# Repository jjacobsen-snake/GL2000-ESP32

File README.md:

# GL2000-ESP32
GL2000 ESP32 WiFi Module

Schematic and PCB designed by me, surrounding [netmindz project](https://github.com/netmindz/balboa_GL_ML_spa_control)

## Pin configuration:
* GPIO 0 - BOOT Button
* GPIO 1 - TxD / USB via FT230XQ
* GPIO 2 - Status LED
* GPIO 3 - RxD / USB via FT230XQ
* GPIO 4 - RD / MAX485E RD
* GPIO 13 - (Pin 4 - Digital pin) Via level shifter
* GPIO 14 - (Pin 5 - Main panel port selector) Via level shifter
* GPIO 16 - RxD2 / MAX485E Tx
* GPIO 17 - TxD2 / MAX485E Rx
* GPIO 21 - SDA / I2C used for BME280, BME680 or SHT45
* GPIO 22 - SCL / I2C used for BME280, BME680 or SHT45

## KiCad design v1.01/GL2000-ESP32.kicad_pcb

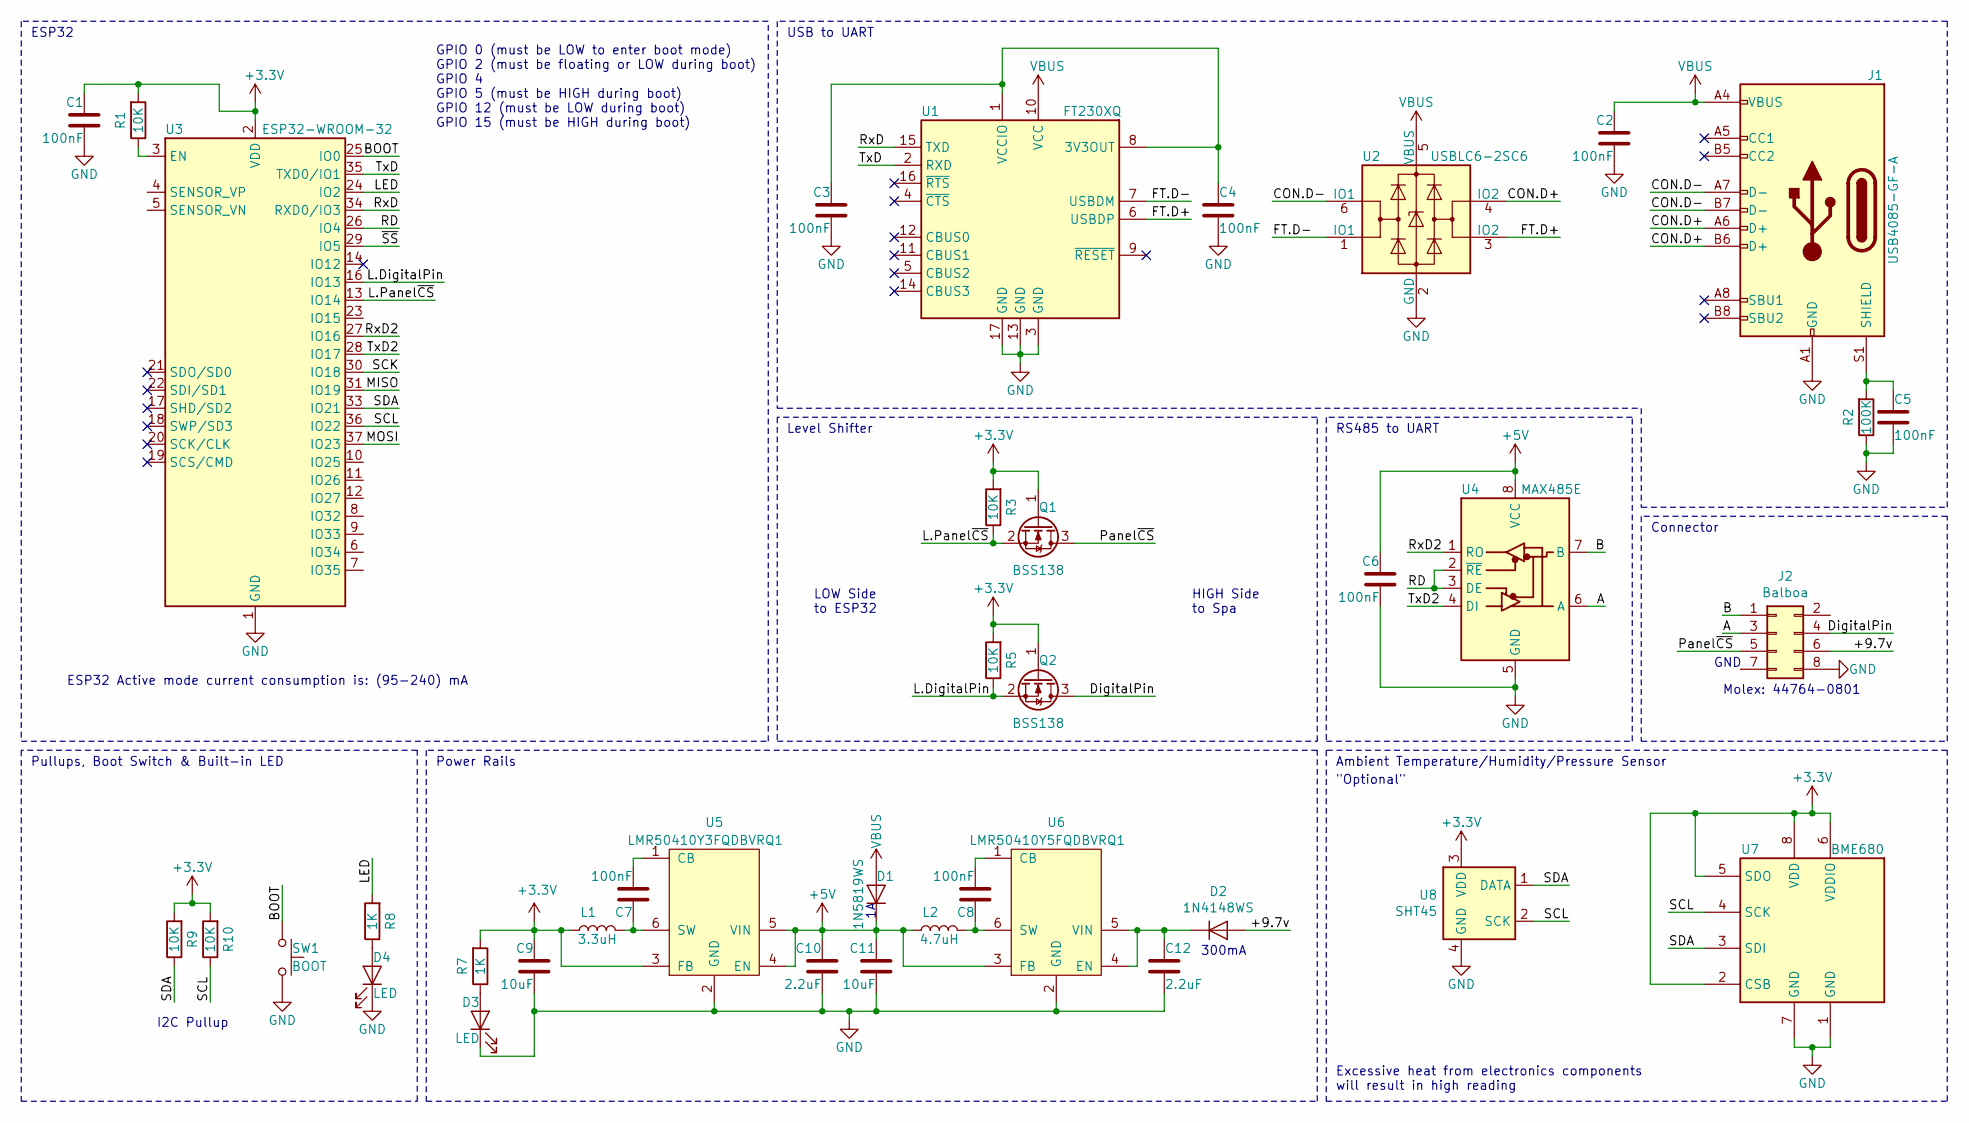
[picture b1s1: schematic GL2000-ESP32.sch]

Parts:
C1, C2, C3, C4, C5, C6, C7, C8: 100nF; C_0805_2012Metric
C9, C11: 10uF; C_0805_2012Metric
C10, C12: 2.2uF; C_0805_2012Metric
D1: 1N5819WS; D_SOD-123
D2: 1N4148WS; D_SOD-123
D3, D4: LED; LED_0805_2012Metric
J1: USB4085-GF-A; USB_C_Receptacle_GCT_USB4085_USB2.0
J2: Balboa; Molex_MicroFit-3.0_44764-0801
L1: 3.3uH; L_0805_2012Metric
L2: 4.7uH; L_0805_2012Metric
Q1, Q2: BSS138; SOT-23
R1, R3, R5, R9, R10: 10K; R_0805_2012Metric
R2: 100K; R_0805_2012Metric
R7, R8: 1K; R_0805_2012Metric
SW1: BOOT; SW_Push_SPST_NO_Alps_SKRK
U1: FT230XQ; QFN-16-1EP_4x4mm_P0.65mm_EP2.1x2.1mm
U2: USBLC6-2SC6; SOT-23-6
U3: ESP32-WROOM-32
U4: MAX485E; SOIC-8_3.9x4.9mm_P1.27mm
U5: LMR50410Y3FQDBVRQ1; SOT-23-6
U6: LMR50410Y5FQDBVRQ1; SOT-23-6
U7: BME680; Bosch_LGA-8_3x3mm_P0.8mm_ClockwisePinNumbering
U8: SHT45; SHT4x

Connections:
+3V3: C1.1, C9.1, L1.2, Q1.1 (G), Q2.1 (G), R1.2, R3.2, R5.2, R7.2, R9.2, R10.2, U3.2 (VDD), U5.3 (FB), U7.2 (CSB), U7.5 (SDO), U7.6 (VDDIO), U7.8 (VDD), U8.3 (VDD)
+5V: C6.1, C10.1, C11.1, D1.1 (K), L2.2, U4.8 (VCC), U5.4 (EN), U5.5 (VIN), U6.3 (FB)
/+9.7v: D2.2 (A), J2.6
/A: J2.3, U4.6 (A)
/B: J2.1, U4.7 (B)
/BOOT: SW1.1, U3.25 (IO0)
/CON.D+: J1.A6 (D+), J1.B6 (D+), U2.4 (IO2)
/CON.D-: J1.A7 (D-), J1.B7 (D-), U2.6 (IO1)
/DigitalPin: J2.4, Q2.3 (D)
/FT.D+: U1.6 (USBDP), U2.3 (IO2)
/FT.D-: U1.7 (USBDM), U2.1 (IO1)
/L.DigitalPin: Q2.2 (S), R5.1, U3.16 (IO13)
/L.Panel~CS: Q1.2 (S), R3.1, U3.13 (IO14)
/LED: R8.2, U3.24 (IO2)
/MISO: U3.31 (IO19)
/MOSI: U3.37 (IO23)
/Panel~CS: J2.5, Q1.3 (D)
/RD: U3.26 (IO4), U4.2 (~RE), U4.3 (DE)
/RxD: U1.15 (TXD), U3.34 (RXD0/IO3)
/RxD2: U3.27 (IO16), U4.1 (RO)
/SCK: U3.30 (IO18)
/SCL: R10.1, U3.36 (IO22), U7.4 (SCK), U8.2 (SCK)
/SDA: R9.1, U3.33 (IO21), U7.3 (SDI), U8.1 (DATA)
/TxD: U1.2 (RXD), U3.35 (TXD0/IO1)
/TxD2: U3.28 (IO17), U4.4 (DI)
/~SS: U3.29 (IO5)
GND: C1.2, C2.2, C3.2, C4.2, C5.2, C6.2, C9.2, C10.2, C11.2, C12.2, D3.1 (K), D4.1 (K), J1.A1 (GND), J1.A12 (GND), J1.B1 (GND), J1.B12 (GND), J2.8, R2.1, SW1.2, U1.3 (GND), U1.13 (GND), U1.17 (GND), U2.2 (GND), U3.1 (GND), U3.15 (GND), U3.38 (GND), U3.39 (GND), U4.5 (GND), U5.2 (GND), U6.2 (GND), U7.1 (GND), U7.7 (GND), U8.4 (GND)
unnamed: C3.1, C4.1, U1.1 (VCCIO), U1.8 (3V3OUT)
unnamed: C5.1, J1.S1 (SHIELD), R2.2
unnamed: C7.1, L1.1, U5.6 (SW)
unnamed: C7.2, U5.1 (CB)
unnamed: C8.1, L2.1, U6.6 (SW)
unnamed: C8.2, U6.1 (CB)
unnamed: C12.1, D2.1 (K), U6.4 (EN), U6.5 (VIN)
unnamed: D3.2 (A), R7.1
unnamed: D4.2 (A), R8.1
unnamed: R1.1, U3.3 (EN)
VBUS: C2.1, D1.2 (A), J1.A4 (VBUS), J1.A9 (VBUS), J1.B4 (VBUS), J1.B9 (VBUS), U1.10 (VCC), U2.5 (VBUS)

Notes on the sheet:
GND
USB to UART
Level Shifter
RS485 to UART
Connector
Ambient Temperature/Humidity/Pressure Sensor
Power Rails
ESP32
Pullups, Boot Switch & Built-in LED
"Optional"
300mA
Molex: 44764-0801
ESP32 Active mode current consumption is: (95-240) mA
GPIO 0 (must be LOW to enter boot mode) GPIO 2 (must be floating or LOW during boot) GPIO 4 GPIO 5 (must be HIGH during boot) GPIO 12 (must be LOW during boot) GPIO 15 (must be HIGH during boot)
I2C Pullup
HIGH Side to Spa
LOW Side to ESP32
Excessive heat from electronics components will result in high reading

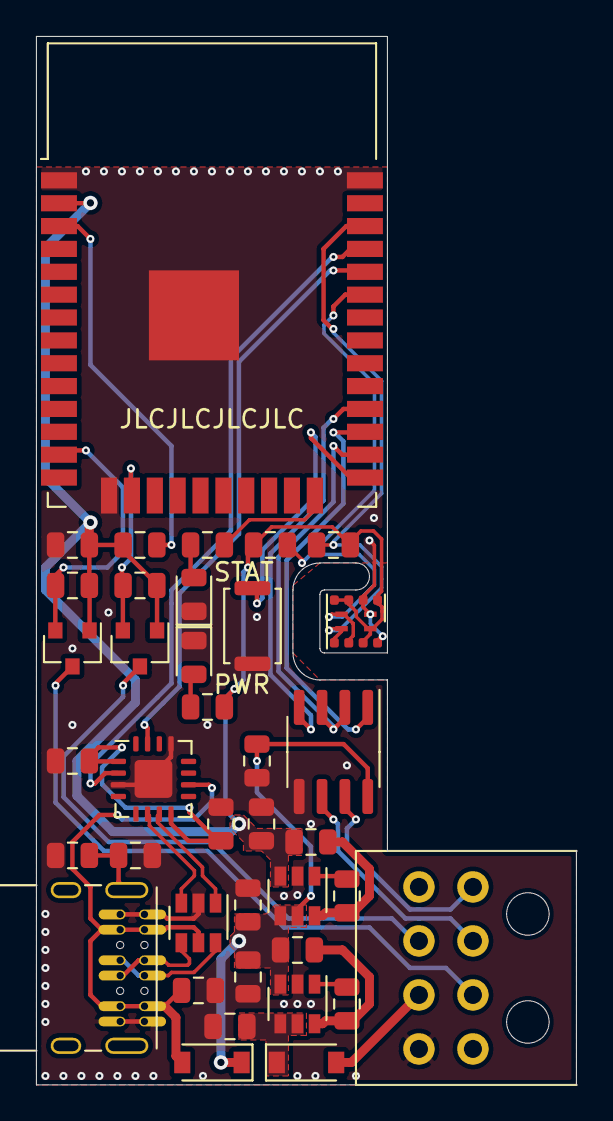
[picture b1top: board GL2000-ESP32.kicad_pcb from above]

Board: 2 copper layers, 30.0 x 58.2 mm, 39 parts (0 on the bottom side), 34 nets.

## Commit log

2023-07-24 Create 1
